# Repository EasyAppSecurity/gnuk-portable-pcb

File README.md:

# gnuk-portable-pcb
Portable GNUK token designed in KiCAD

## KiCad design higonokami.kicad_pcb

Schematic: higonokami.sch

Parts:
C2, C3, C4: 0.1uF
C5, C10: 10nF
C6, C7: CSMALL
C8, C9: 4.7uF
D1: LED
J1: USB
P1: CONN_5
Q1: BC857; SOT-23
R1, R2: 22R
R3, R5: 1.5k
R4: 10k
U1: STM32F103CB; LQFP48
U2: LD3985G33R; TSOT-23-5
X1: 12MHz

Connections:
+3.3V: C2.1, C3.1, C4.1, C5.1, C9.1, P1.2, Q1.3 (C), U1.1 (VBAT), U1.9 (VDDA), U1.24 (VDD), U1.36 (VDD), U1.48 (VDD), U2.5 (VOUT)
GND: C2.2, C3.2, C4.2, C5.2, C6.2, C7.2, C8.2, C9.2, C10.2, D1.2 (K), J1.4 (GND), J1.5 (Shield_1), J1.6 (Shield_2), P1.1, U1.8 (VSSA), U1.20 (PB2/BOOT1), U1.23 (VSS), U1.35 (VSS), U1.47 (VSS), U2.2 (GND), X1.3 (GND)
unnamed: Q1.2 (E), R3.1
unnamed: J1.2 (D-), R2.1
unnamed: P1.4, U1.30 (USART1_TX/TIM1_CH2/PA9)
unnamed: P1.5, U1.31 (USART1_RX/TIM1_CH3/PA10)
unnamed: R1.2, R3.2, U1.33 (USART1_RTS/CANTX/USBDP/TIM1_ETR/PA12)
unnamed: J1.3 (D+), R1.1
unnamed: R2.2, U1.32 (USART1_CTS/CANRX/USBDM/TIM1_CH4/PA11)
unnamed: C8.1, J1.1 (Vbus), U2.1 (VIN), U2.3 (INH)
unnamed: R5.1, U1.18 (PB0/ADC12_IN8/TIM3_CH3)
unnamed: D1.1 (A), R5.2
unnamed: C6.1, U1.5 (PD0/OSC_IN), X1.1
unnamed: C10.1, U2.4 (BYP)
unnamed: R4.1, U1.29 (USART1_CK/TIM1_CH1/MCO/PA8)
unnamed: Q1.1 (B), R4.2
unnamed: C7.1, U1.6 (PD1/OSC_OUT), X1.2
unnamed: P1.3, U1.44 (BOOT0)

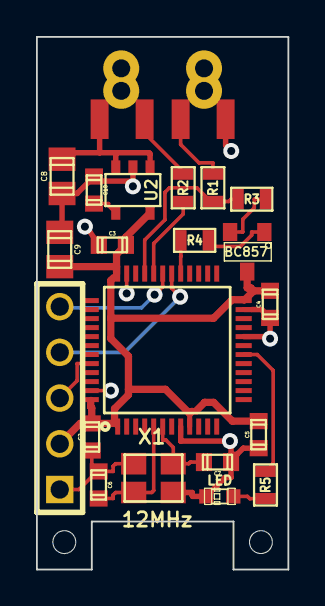
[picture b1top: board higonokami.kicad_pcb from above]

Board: 2 copper layers, 14.0 x 29.6 mm, 23 parts (0 on the bottom side), 18 nets.

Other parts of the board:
PINHOLE, PINHOLE2: VAL**; PINHOLE

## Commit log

2016-01-20 Initial commit of higonokami STM32-based USB dongle (for Gnuk)
2018-05-20 add readme
